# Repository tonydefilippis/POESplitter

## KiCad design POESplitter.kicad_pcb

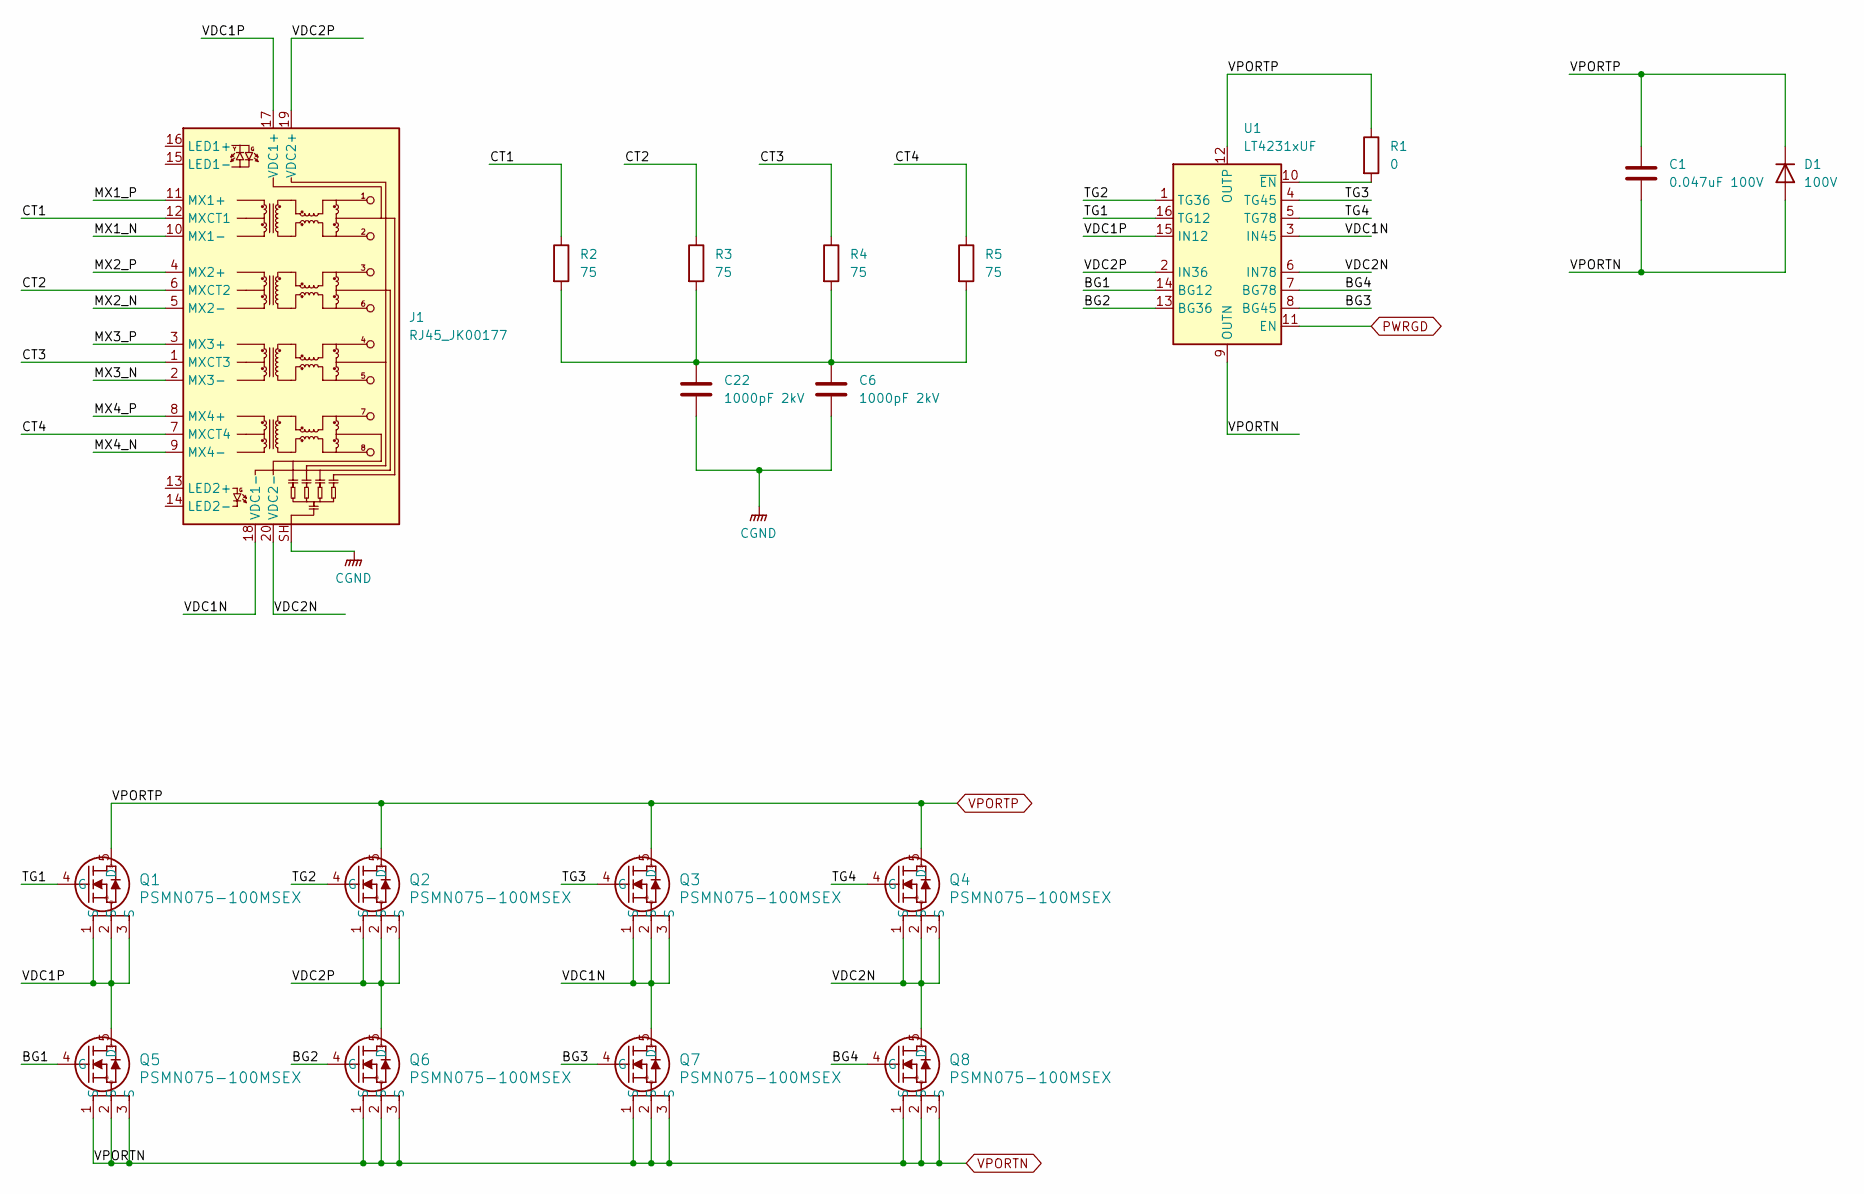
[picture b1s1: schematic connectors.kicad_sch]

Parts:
C1: 0.047uF 100V; 0603
C6, C22: 1000pF 2kV; 0603
D1: 100V; 0603
J1: RJ45_JK00177; RJ45_Pulse_JK00177NL_Horizontal
Q1, Q2, Q3, Q4, Q5, Q6, Q7, Q8: PSMN075-100MSEX; LFPAK33_SOT1210_NEX
R1: 0; 0603
R2, R3, R4, R5: 75; 0603
U1: LT4231xUF; QFN-16-1EP_4x4mm_P0.65mm_EP2.15x2.15mm

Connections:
/Connectors/BG1: Q5.4 (G), U1.14 (BG12)
/Connectors/BG2: Q6.4 (G), U1.13 (BG36)
/Connectors/BG3: Q7.4 (G), U1.8 (BG45)
/Connectors/BG4: Q8.4 (G), U1.7 (BG78)
/Connectors/CT1: J1.12 (MXCT1), R2.1
/Connectors/CT2: J1.6 (MXCT2), R3.1
/Connectors/CT3: J1.1 (MXCT3), R4.1
/Connectors/CT4: J1.7 (MXCT4), R5.1
/Connectors/MX1_N: J1.10 (MX1-)
/Connectors/MX1_P: J1.11 (MX1+)
/Connectors/MX2_N: J1.5 (MX2-)
/Connectors/MX2_P: J1.4 (MX2+)
/Connectors/MX3_N: J1.2 (MX3-)
/Connectors/MX3_P: J1.3 (MX3+)
/Connectors/MX4_N: J1.9 (MX4-)
/Connectors/MX4_P: J1.8 (MX4+)
/Connectors/TG1: Q1.4 (G), U1.16 (TG12)
/Connectors/TG2: Q2.4 (G), U1.1 (TG36)
/Connectors/TG3: Q3.4 (G), U1.4 (TG45)
/Connectors/TG4: Q4.4 (G), U1.5 (TG78)
/Connectors/VDC1N: J1.18 (VDC1-), Q3.1 (S), Q3.2 (S), Q3.3 (S), Q7.5 (D), U1.3 (IN45)
/Connectors/VDC1P: J1.17 (VDC1+), Q1.1 (S), Q1.2 (S), Q1.3 (S), Q5.5 (D), U1.15 (IN12)
/Connectors/VDC2N: J1.20 (VDC2-), Q4.1 (S), Q4.2 (S), Q4.3 (S), Q8.5 (D), U1.6 (IN78)
/Connectors/VDC2P: J1.19 (VDC2+), Q2.1 (S), Q2.2 (S), Q2.3 (S), Q6.5 (D), U1.2 (IN36)
CGND: C6.2, C22.2, J1.SH
unnamed: C6.1, C22.1, R2.2, R3.2, R4.2, R5.2
unnamed: R1.2, U1.10 (~EN)
PWRGD: U1.11 (EN)
VPORTN: C1.2, D1.2 (A), Q5.1 (S), Q5.2 (S), Q5.3 (S), Q6.1 (S), Q6.2 (S), Q6.3 (S), Q7.1 (S), Q7.2 (S), Q7.3 (S), Q8.1 (S), Q8.2 (S), Q8.3 (S), U1.9 (OUTN), U1.17 (OUTN); also elsewhere on the board
VPORTP: C1.1, D1.1 (K), Q1.5 (D), Q2.5 (D), Q3.5 (D), Q4.5 (D), R1.1, U1.12 (OUTP); also elsewhere on the board

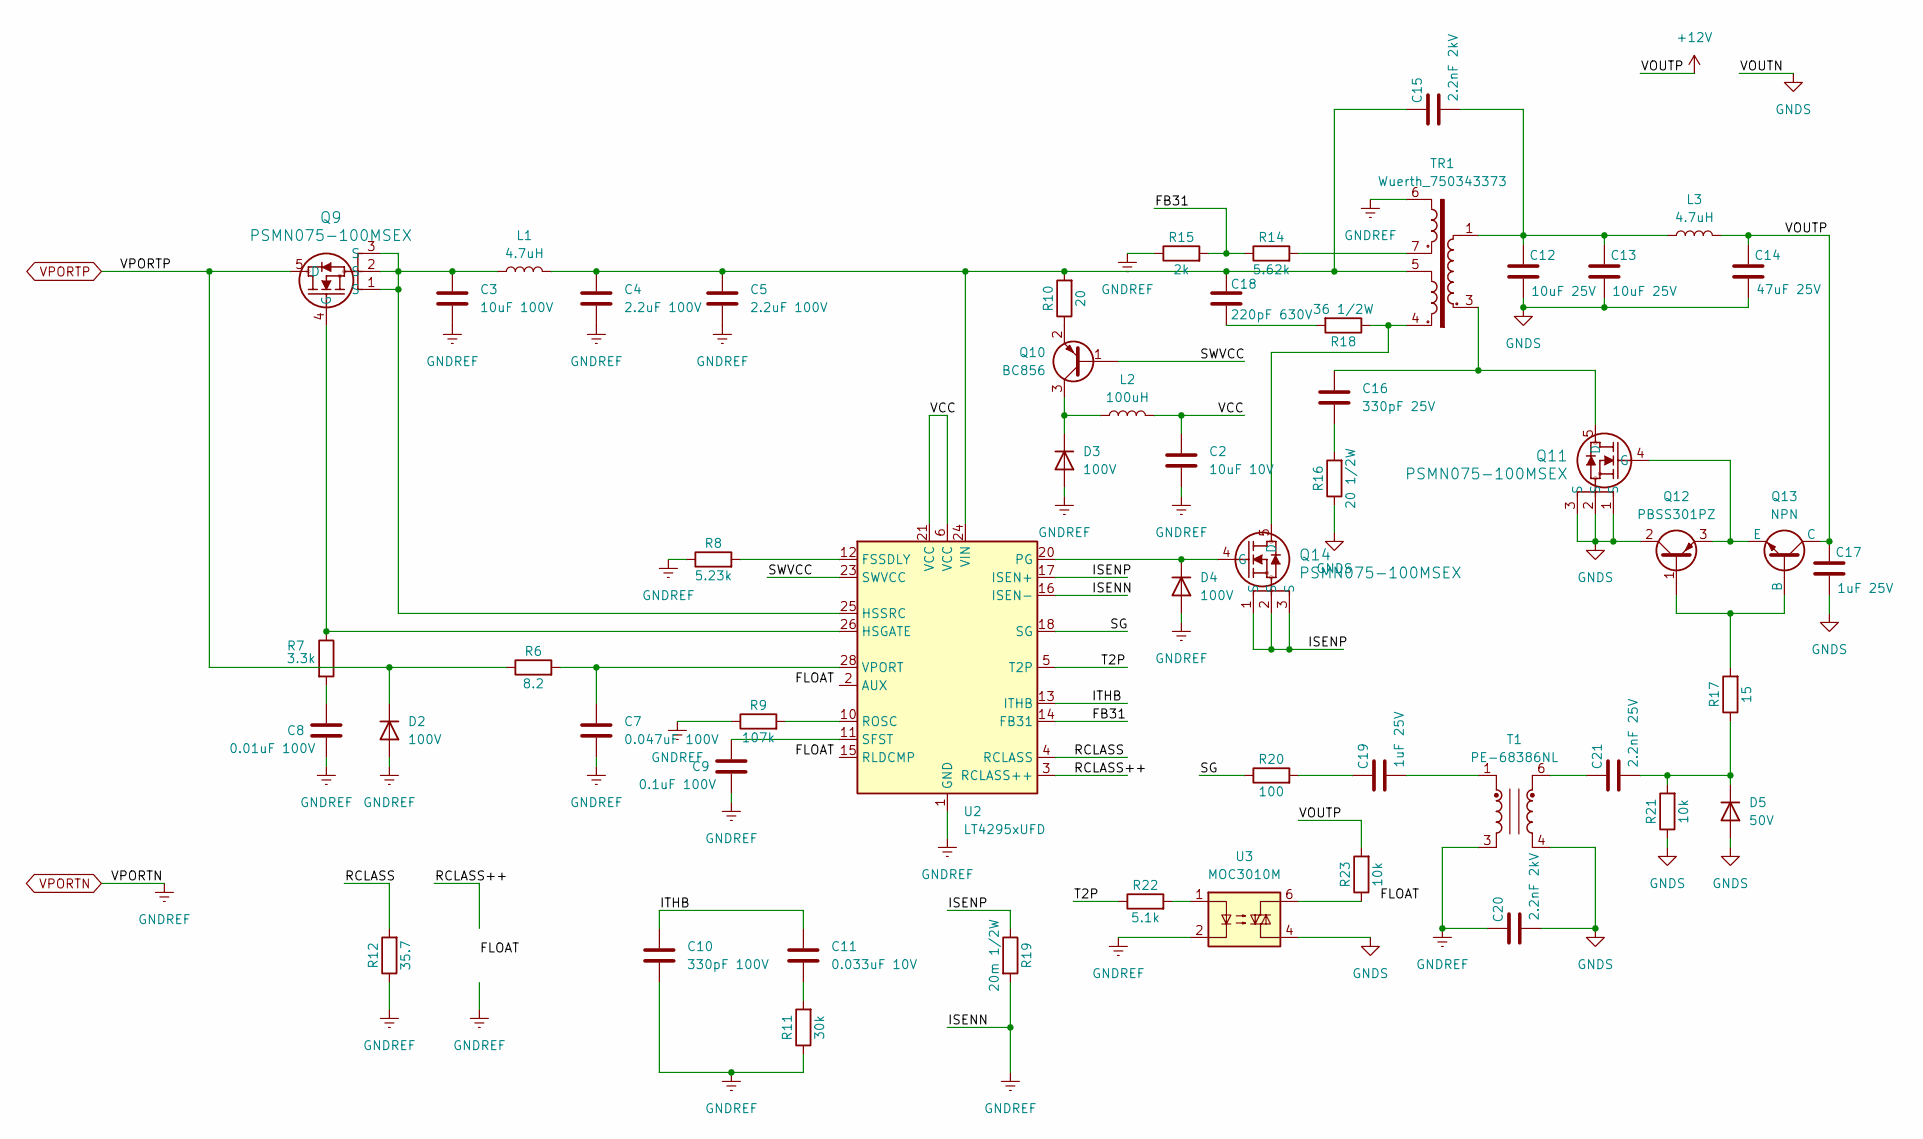
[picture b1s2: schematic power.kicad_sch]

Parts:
C2: 10uF 10V; 0603
C3: 10uF 100V; 0603
C4, C5: 2.2uF 100V; 0603
C7: 0.047uF 100V; 0603
C8: 0.01uF 100V; 0603
C9: 0.1uF 100V; 0603
C10: 330pF 100V; 0603
C11: 0.033uF 10V; 0603
C12, C13: 10uF 25V; 0603
C14: 47uF 25V; 0603
C15, C20: 2.2nF 2kV; 0603
C16: 330pF 25V; 0603
C17, C19: 1uF 25V; 0603
C18: 220pF 630V; 0603
C21: 2.2nF 25V; 0603
D2, D3, D4: 100V; 0603
D5: 50V; 0603
L1, L3: 4.7uH
L2: 100uH
Q9, Q11, Q14: PSMN075-100MSEX; LFPAK33_SOT1210_NEX
Q10: BC856; SOT-23
Q12: PBSS301PZ; SOT-223-3_TabPin2
Q13: NPN
R6: 8.2; 0603
R7: 3.3k; 0603
R8: 5.23k; 0603
R9: 107k; 0603
R10: 20; 0603
R11: 30k; 0603
R12: 35.7; 0603
R14: 5.62k; 0603
R15: 2k; 0603
R16: 20 1/2W; 0603
R17: 15; 0603
R18: 36 1/2W; 0603
R19: 20m 1/2W; 0603
R20: 100; 0603
R21, R23: 10k; 0603
R22: 5.1k; 0603
T1: PE-68386NL; Pulse_PA2001NL
TR1: Wuerth_750343373; Transformer_Wuerth_750343373
U2: LT4295xUFD; QFN-28-1EP_4x5mm_P0.5mm_EP2.65x3.65mm
U3: MOC3010M

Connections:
+12V: C14.2, C17.2, L3.2, Q13.1 (C), R23.2
/Power/FB31: R14.1, R15.2, U2.14 (FB31)
/Power/ISENP: Q14.1 (S), Q14.2 (S), Q14.3 (S), R19.1, U2.17 (ISEN+)
/Power/ITHB: C10.2, C11.2, U2.13 (ITHB)
/Power/RCLASS: R12.2, U2.4 (RCLASS)
/Power/RCLASS++: U2.3 (RCLASS++); also elsewhere on the board
/Power/SG: R20.1, U2.18 (SG)
/Power/SWVCC: Q10.1 (B), U2.23 (SWVCC)
/Power/T2P: R22.1, U2.5 (T2P)
/Power/VCC: C2.1, L2.2, U2.6 (VCC), U2.7 (VCC), U2.8 (VCC), U2.9 (VCC), U2.21 (VCC)
GNDS: C12.1, C13.1, C14.1, C17.1, C20.1, D5.2 (A), Q11.1 (S), Q11.2 (S), Q11.3 (S), Q12.2 (C), Q12.4 (C), R16.1, R21.1, T1.4, U3.4
unnamed: C8.1, R7.2
unnamed: C11.1, R11.2
unnamed: C12.2, C13.2, C15.1, L3.1, TR1.1
unnamed: C16.2, R16.2
unnamed: C18.2, R18.2
unnamed: C19.1, T1.1
unnamed: C19.2, R20.2
unnamed: C21.2, T1.6
unnamed: D3.1 (K), L2.1, Q10.3 (C)
unnamed: D4.1 (K), Q14.4 (G), U2.20 (PG)
unnamed: C21.1, D5.1 (K), R17.1, R21.2
unnamed: Q9.4 (G), R7.1, U2.26 (HSGATE)
unnamed: Q10.2 (E), R10.1
unnamed: C16.1, Q11.5 (D), TR1.3
unnamed: Q11.4 (G), Q12.3 (E), Q13.3 (E)
unnamed: Q12.1 (B), Q13.2 (B), R17.2
unnamed: Q14.5 (D), R18.1, TR1.4
unnamed: R14.2, TR1.7
unnamed: R22.2, U3.1
unnamed: R23.1, U3.6
unnamed: R8.2, U2.12 (FSSDLY)
unnamed: C3.2, L1.1, Q9.1 (S), Q9.2 (S), Q9.3 (S), U2.25 (HSSRC)
unnamed: R9.2, U2.10 (ROSC)
unnamed: C9.1, U2.11 (SFST)
unnamed: C4.2, C5.2, C15.2, C18.1, L1.2, R10.2, TR1.5, U2.24 (VIN)
unnamed: C7.2, R6.2, U2.28 (VPORT)
VPORTN: C2.2, C3.1, C4.1, C5.1, C7.1, C8.2, C9.2, C10.1, C20.2, D2.2 (A), D3.2 (A), D4.2 (A), R8.1, R9.1, R11.1, R12.1, R15.1, R19.2, T1.3, TR1.6, U2.1 (GND), U2.16 (ISEN-), U2.19 (GND), U2.29 (GND), U3.2; also elsewhere on the board
VPORTP: D2.1 (K), Q9.5 (D), R6.1; also elsewhere on the board

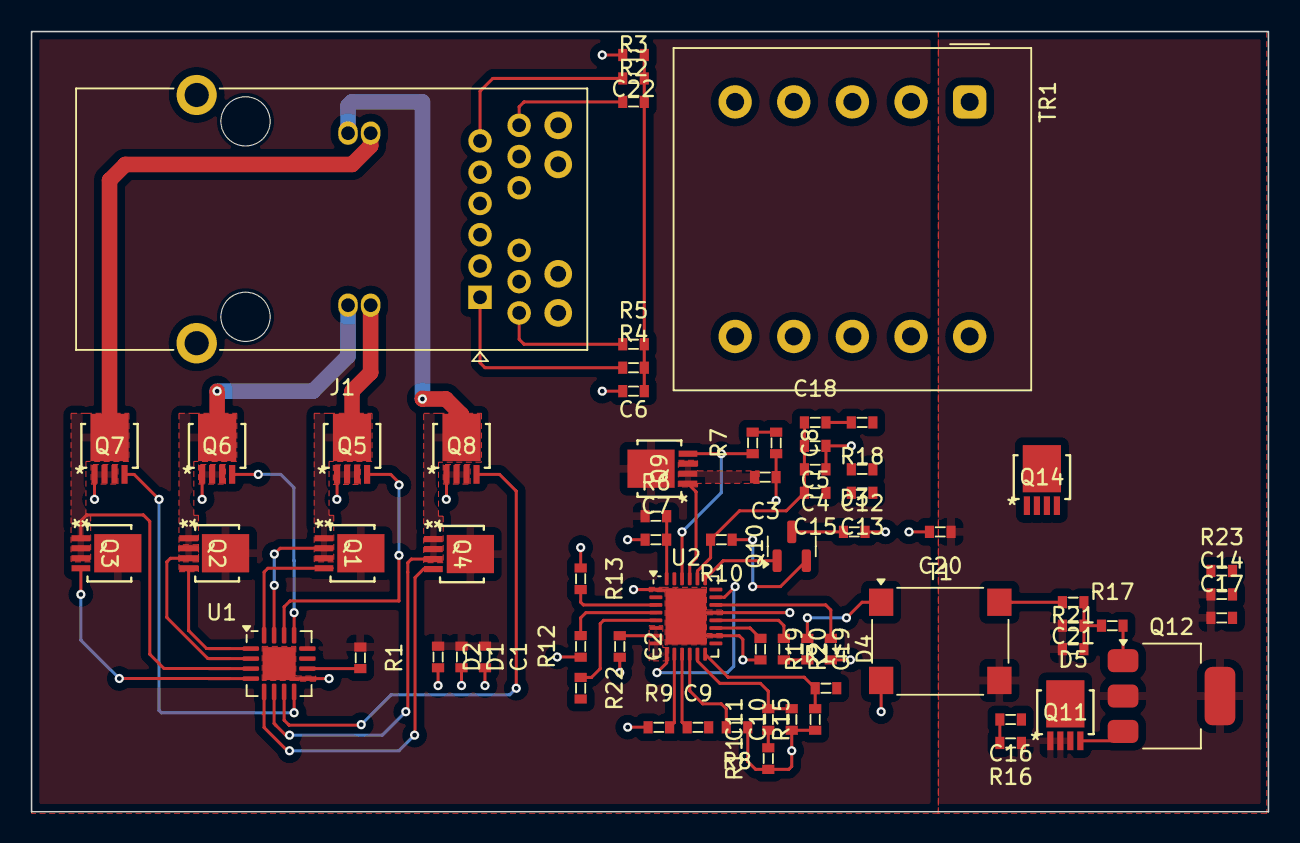
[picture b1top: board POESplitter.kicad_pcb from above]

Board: 4 copper layers, 80.4 x 50.7 mm, 68 parts (0 on the bottom side), 56 nets.

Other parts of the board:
R13: 150; 0603

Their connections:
/Power/RCLASS++: R13.2; also elsewhere on the board
VPORTN: R13.1; also elsewhere on the board

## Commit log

2024-10-11 Initial commit of local project.
